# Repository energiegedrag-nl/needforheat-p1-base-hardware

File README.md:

# NeedForHeat P1-BASE hardware <!-- omit in toc -->

This repository contains the open hardware design files for the NeedForHeat P1-BASE, an extension module (BASE) for the back of an [M5Stack CoreInk](https://docs.m5stack.com/en/core/coreink). With it, the CoreInk reads [smart meters that adhere to the Dutch Smart Meter Requirements](https://github.com/energiegedrag-nl/dsmr-info) via the [P1 port](https://nl.wikipedia.org/wiki/P1-poort), while an existing P1 reader of the household keeps working.

> **Own deployment.** This repository is maintained by [energiegedrag-nl](https://github.com/energiegedrag-nl) and deployed under `energiegedrag.nl`. To run your own instance, replace `energiegedrag-nl` by your GitHub organisation and `energiegedrag.nl` by your domain (hosts used: `api.<domain>`, `manuals.<domain>`), consistently in configuration and build settings.

> **Version 3.0 (November 2026) is a design that has not been built or tested yet.** The previous version 2.7 (June 2024, with DIP switches) is available under the git tag `v2.7`. See [docs/design-v3.md](docs/design-v3.md) for the design and the list of points to verify on the first prototype.

*Top edge: smart-meter socket `J2` with its green LED, which shows through a window in the top wall of the tray. The lower socket `J3` has its own green LED in the bottom wall.*

## Table of contents <!-- omit in toc -->
- [General info](#general-info)
- [Producing](#producing)
  - [Printed Circuit Board](#printed-circuit-board)
  - [Enclosure](#enclosure)
- [Deploying](#deploying)
  - [Cost](#cost)
  - [Connecting](#connecting)
  - [Indicators](#indicators)
- [Developing](#developing)
- [Features](#features)
- [Status](#status)
- [License](#license)
- [Citation](#citation)
- [Credits](#credits)

## General info

The P1-BASE plugs into the 2x8 MI-BUS socket on the back of the CoreInk. The upper RJ12 socket (`J2`, *smart meter*) connects to the P1 port of the smart meter; the lower RJ12 socket (`J3`, *other P1 reader*) takes the cable of an existing P1 reader, as if it were connected to the meter itself.

In short (details in [docs/design-v3.md](docs/design-v3.md)):

* **Meter input** with a 1 kΩ pull-up and a Schmitt trigger, as in the v2.7 front end that read Landis+Gyr E350/E360 meters in the lab.
* **Active splitter**, powered by the meter: an existing reader keeps getting data when the CoreInk is off, asleep or crashed.
* **Data request** without DIP switches: the CoreInk (G26) and the existing reader can both request data; firmware can see whether the reader requests (G34).
* **Power from the P1 port**: on DSMR 5 meters the BASE can charge the CoreInk battery at 60 or 120 mA, switched by firmware and with a soft start that stays below the meter's fold-back limit.
* **Robust installation**: a crossed RJ12 cable or a cable in the wrong socket does no harm, and the firmware can tell which mistake was made.

The firmware is [needforheat-p1-reader-firmware](https://github.com/energiegedrag-nl/needforheat-p1-reader-firmware) (PlatformIO environment `M5STACK_COREINK_P1BASE_V3`).

## Producing

### Printed Circuit Board

The folder [pcb/jlcpcb](./pcb/jlcpcb) contains the files to have the PCB manufactured *and assembled* by [JLCPCB](https://jlcpcb.com); no soldering is needed:

1. Upload [`GERBER-needforheat-p1-base-hardware.zip`](./pcb/jlcpcb/GERBER-needforheat-p1-base-hardware.zip) on the [JLCPCB quote page](https://cart.jlcpcb.com/quote). Defaults are fine (2 layers, 1.6 mm).
2. Select *PCB Assembly*, top side, and upload [`BOM-needforheat-p1-base-hardware.csv`](./pcb/jlcpcb/BOM-needforheat-p1-base-hardware.csv) and [`CPL-needforheat-p1-base-hardware.csv`](./pcb/jlcpcb/CPL-needforheat-p1-base-hardware.csv).
3. The three through-hole parts (two RJ12 sockets, the 2x8 stacking header) are soldered by JLCPCB as well; accept the through-hole assembly option.
4. `R6` and `R15` are intentionally not fitted (see [assembly variants](docs/design-v3.md#8-production)).

Schematic and layout printouts: [docs/needforheat-p1-base-hardware-sch.pdf](docs/needforheat-p1-base-hardware-sch.pdf) and [docs/needforheat-p1-base-hardware-pcb.pdf](docs/needforheat-p1-base-hardware-pcb.pdf).

### Enclosure

The folder [enclosure](./enclosure) contains a parametric enclosure (CadQuery script) and exported STEP/STL files in [enclosure/fabrication](./enclosure/fabrication): a tray (*kuip*) that holds the PCB and a lid that clicks onto it (snap fit, no screws). The outside is exactly the CoreInk's outline (40 x 56 mm), so any BASE that fits a bare CoreInk also fits behind the P1-BASE. Four posts with crush ribs centre the module in the CoreInk's LEGO-compatible holes; the lid repeats those holes as LEGO Technic holes and has the bus socket just below its surface (0.3 mm), like the CoreInk's back; feet under the lid's corners hold the PCB down. Each socket's LED shows through a window in the wall next to it; an arrow on the lid points to the meter edge. Each module fits a letterbox parcel on its own (at most 27 mm thick). Print with PETG or let a 3D printing service make them (SLA resin or MJF nylon).

## Deploying

### Cost

Indicative, November 2026, excluding VAT and shipping. JLCPCB quotes (LeadFree HASL, top side, no panelisation;
5 pieces on 17 November after the design review, the rest on 16 November 2026; the review changed only resistor
values and J1's drill, which hardly changes the price) for the same quantities as the
[BatteryBASE](https://github.com/energiegedrag-nl/needforheat-battery-base-hardware#cost). Everything is assembled
by JLCPCB, the through-hole parts included: the quotes contain the hand-soldering fee (€ 3.27 per order) and the
per-joint manual assembly of the RJ12 jacks. The stacking header J1 (Samtec ESQ-108-24-G-D, C21241050) is not in
JLCPCB's stock: it is bought through JLCPCB's *Global Sourcing* into the account's parts library (9–15 days or more;
the prototype's seven arrive on 8 December 2026) and then assembled by JLCPCB (Samtec rates it for lead wave soldering only, so the order asks for hand
soldering with the pins kept free of solder; Economic and Standard PCBA). The J1 column adds its Global Sourcing price (€ 6.28 each, the price of the prototype's order),
its extended-part loading fee (€ 3.16 per order) and the soldering of its 16 joints (about € 0.26 per board,
JLCPCB's [per-joint rate](https://jlcpcb.com/help/article/PCB-assembly-faqs) of $ 0.0173); to be confirmed by the
quote with J1 once it is in the parts library.

| Quantity | PCBA type | PCB + PCBA without J1 | J1 (part, fee, soldering) | Per board | Enclosure (tray, lid) per set |
|---:|---|---:|---:|---:|---:|
| 5 | Economic | € 59.50 | € 35.84 | € 19.07 | $ 3.32 |
| 10 | Economic | € 79.26 | € 68.52 | € 14.78 | $ 3.32 |
| 30 | Economic | € 157.92 | € 199.24 | € 11.91 | $ 3.32 |
| 100 | Standard (Economic not offered) | € 274.37 + U5 € 185.94 | € 656.76 | € 11.17 | $ 3.32 |

J1 is the most expensive part by far. For larger series it is worth buying it cheaper: Samtec lists $ 4.10 each at
25 and $ 3.39 at 100, and JLCPCB's pre-order price is € 3.67 when a pre-order goes through (the prototype's
pre-order of 15 November 2026 was cancelled and refunded). Global Sourcing has to be ordered at least 10 pieces at a
time in the parts cart (the prototype's order of seven went through at checkout).

At 100 pieces JLCPCB had only 62 PCA9633 LED dimmers (U5) in stock: the € 274.37 is without U5, which adds about
€ 1.86 per board at JLCPCB's part price once it is in stock again. The PCA9633 is also the most expensive part at
small quantities (€ 2.78 at 5, € 2.36 at 10). Enclosure: MJF nylon prints (PA12, dyed black), which JLC3DP prices
per piece, so the price per set does not depend on the quantity (17 November 2026: tray $ 1.62, lid $ 1.70; the
prototype order adds a second lid with a firmer snap fit, $ 1.70). Shipping to the Netherlands adds about € 20–25 per
order.

| Item | Approx. price |
|---|---:|
| P1-BASE PCB, assembled (JLCPCB), J1 included | € 11–19 (see above) |
| Enclosure (3D printed, MJF nylon) | € 3 |
| M5Stack CoreInk | € 36 |
| RJ12 cable 6P6C, straight (1:1), ≤ 0.5 m | € 3–6 |
| USB power adapter (only for DSMR 2/3 meters) | € 10–15 |

### Connecting

The CoreInk and the P1-BASE are shipped separately (each fits a letterbox parcel) and clicked together at home.

1. Hold the CoreInk with its screen facing you and the HAT connector (top edge) up. Push the P1-BASE onto its back so that the *smart meter* socket is at the top (the arrow on the lid points up); it only fits this way round.
2. Unplug an existing P1 reader (if any) from the smart meter.
3. Plug the supplied **straight (1:1)** RJ12 cable into the *smart meter* socket and into the P1 port of the smart meter. Do not use a telephone cable: those are crossed. A crossed cable does no damage, but nothing works; the screen will say so.
4. Plug the existing P1 reader into the lower *other P1 reader* socket.

With a DSMR 2 or 3 meter (no power on the P1 port), also connect the USB power adapter to the CoreInk.

### Indicators

Each socket has a green light next to it: **it blinks when data goes over that cable.**

| Green light next to | Blinks | Stays dark (or lights steadily): check |
|---|---|---|
| *smart meter* socket (top) | the meter sends data | the cable to the meter; whether the meter's P1 port is enabled (with no cable, or a meter that is not asked for data, it can light steadily) |
| *other P1 reader* socket (bottom) | the existing P1 reader asks for data and gets it | whether a reader is plugged in and powered; its cable |

Charging the CoreInk battery from the P1 port (DSMR 5 meters) is shown on the screen.

Firmware can dim both LEDs together or switch them off (I²C LED driver, see [LED dimmer](docs/design-v3.md#47-led-dimmer)); the hardware still decides when each LED is on. The driver is powered by the meter, so the setting survives while the CoreInk sleeps or is off; until firmware sets it (and after the meter's power was lost), the LEDs light at full brightness.

## Developing

You need [KiCad 10](https://www.kicad.org/download/) to change the design; the KiCad files are in [pcb](./pcb).

The schematic and the board are generated by scripts in [tools](./tools), so that the netlist, the placement and the documentation stay consistent:

* `python tools/gen_schematic.py` writes the schematic and the custom symbol library from the circuit description in the script.
* `"<KiCad>/bin/python.exe" tools/gen_pcb.py` builds the board from the schematic netlist, places the parts and routes the board with [Freerouting](https://github.com/freerouting/freerouting) (Java 25 needed).
* `python tools/sim/run_sims.py` runs SPICE checks with the ngspice library that ships with KiCad and writes [docs/simulation](docs/simulation).
* `python tools/export_fab.py` writes the JLCPCB files and the PDF printouts.
* 3D models in `pcb/p1base.3dshapes`: J1 is Samtec's own model of the ESQ-108-24-G-D (downloaded from the
  [product page](https://www.samtec.com/products/esq-108-24-g-d), provided "as is"; placed by
  `python tools/import_samtec_j1.py <esq-108-24-g-d.stp>`). EVERCOM publishes no 3D model of the RJ12 jack
  5301-6P6C, so `python tools/gen_3d_models.py` builds an approximate one from its drawing (5301-660XXX rev. A).

You may also edit the KiCad files by hand; then stop using the generators or port your changes into them.

## Features

Ready (in the design, not yet verified on hardware):

- [x] Active P1 splitter powered by the meter, open-drain output as DSMR prescribes.
- [x] Data request by firmware and by the existing reader (hardware OR); read-back of the reader's request.
- [x] Charging the CoreInk battery from DSMR 5 meters at 60/120 mA with soft start.
- [x] Protection against crossed cables and ESD; meter voltage measurement for diagnosis.
- [x] A green LED next to each socket that blinks when data goes over that cable; dimmable by firmware (one common level); test points.
- [x] All parts on the top side; full assembly by JLCPCB.
- [x] Enclosure flush with the CoreInk outline, so other CoreInk BASEs still stack behind it; snap-fit lid with LEGO Technic holes.

To-do:

- [ ] Build and test a first prototype (see [the list of points to verify](docs/design-v3.md#10-open-points-to-verify)), including Landis+Gyr E360 meters and common P1 readers on the second socket.

## Status

Project is: _in progress_ (v3.0 design; v2.7 built and lab-tested in 2024).

## License

The hardware designs in this repository are available under the [CERN-OHL-P v2 license](./LICENSE).
Copyright 2024 [Research group Energy Transition, Windesheim University of Applied Sciences](https://windesheim.nl/energietransitie) (up to v2.7); copyright 2026 Henri ter Hofte (v3.0).

## Citation

If you use this repository in your research or work, please cite the following pre-print, which describes the overall NeedForHeat DataGear system of which this repository is a part:

> Ter Hofte, H., & van Ravenzwaaij, N. (2025). *NeedForHeat DataGear: An Open Monitoring System to Accelerate the Residential Heating Transition*. arXiv preprint arXiv:2509.06927. https://doi.org/10.48550/arXiv.2509.06927

**Note:** This is a pre-print submitted on 8 Sep 2025 and has not yet been peer-reviewed. For the full paper, see [https://arxiv.org/abs/2509.06927](https://arxiv.org/abs/2509.06927).

## Credits

Version 3.0:
* Henri ter Hofte · [@henriterhofte](https://github.com/henriterhofte)

Version 2.7 and earlier, made at the Research group Energy Transition, Windesheim University of Applied Sciences, as a collaborative effort of:
* Rick de Graaf · [@277r](https://github.com/277r)
* Gerwin ten Have · [@GerwintenHave](https://github.com/GerwintenHave)

with product owners:
* Henri ter Hofte · [@henriterhofte](https://github.com/henriterhofte)
* Marco Winkelman · [@MarcoW71](https://github.com/MarcoW71)

We use and gratefully acknowledge the efforts of the makers of:
* [Twomes P1 Gateway Hardware](https://github.com/energiegedrag-nl/twomes-p1-gateway-hardware), by Research group Energy Transition at Windesheim University of Applied Sciences, licensed under Apache 2.0
* [KiCad Libraries](https://kicad.github.io/), by the KiCad Development Team, licensed under [an adapted version of the CC-BY-SA 4.0 License](https://www.kicad.org/libraries/license/)
* [Freerouting](https://github.com/freerouting/freerouting), licensed under GPL-3.0 (used as a tool; no code included)
* [ngspice](https://ngspice.sourceforge.io/) and [CadQuery](https://github.com/CadQuery/cadquery) (used as tools)
* The mechanical data of the [M5Stack CoreInk](https://github.com/m5stack/M5_Hardware), by M5Stack

### AI assistance

Since November 2026, parts of this repository (the v3.0 design, its generators and documentation) have been made with [Claude Code](https://claude.com/claude-code) (Anthropic), under the author's direction and review. Commits made this way carry a `Co-Authored-By: Claude …` trailer. The author remains responsible for all content.

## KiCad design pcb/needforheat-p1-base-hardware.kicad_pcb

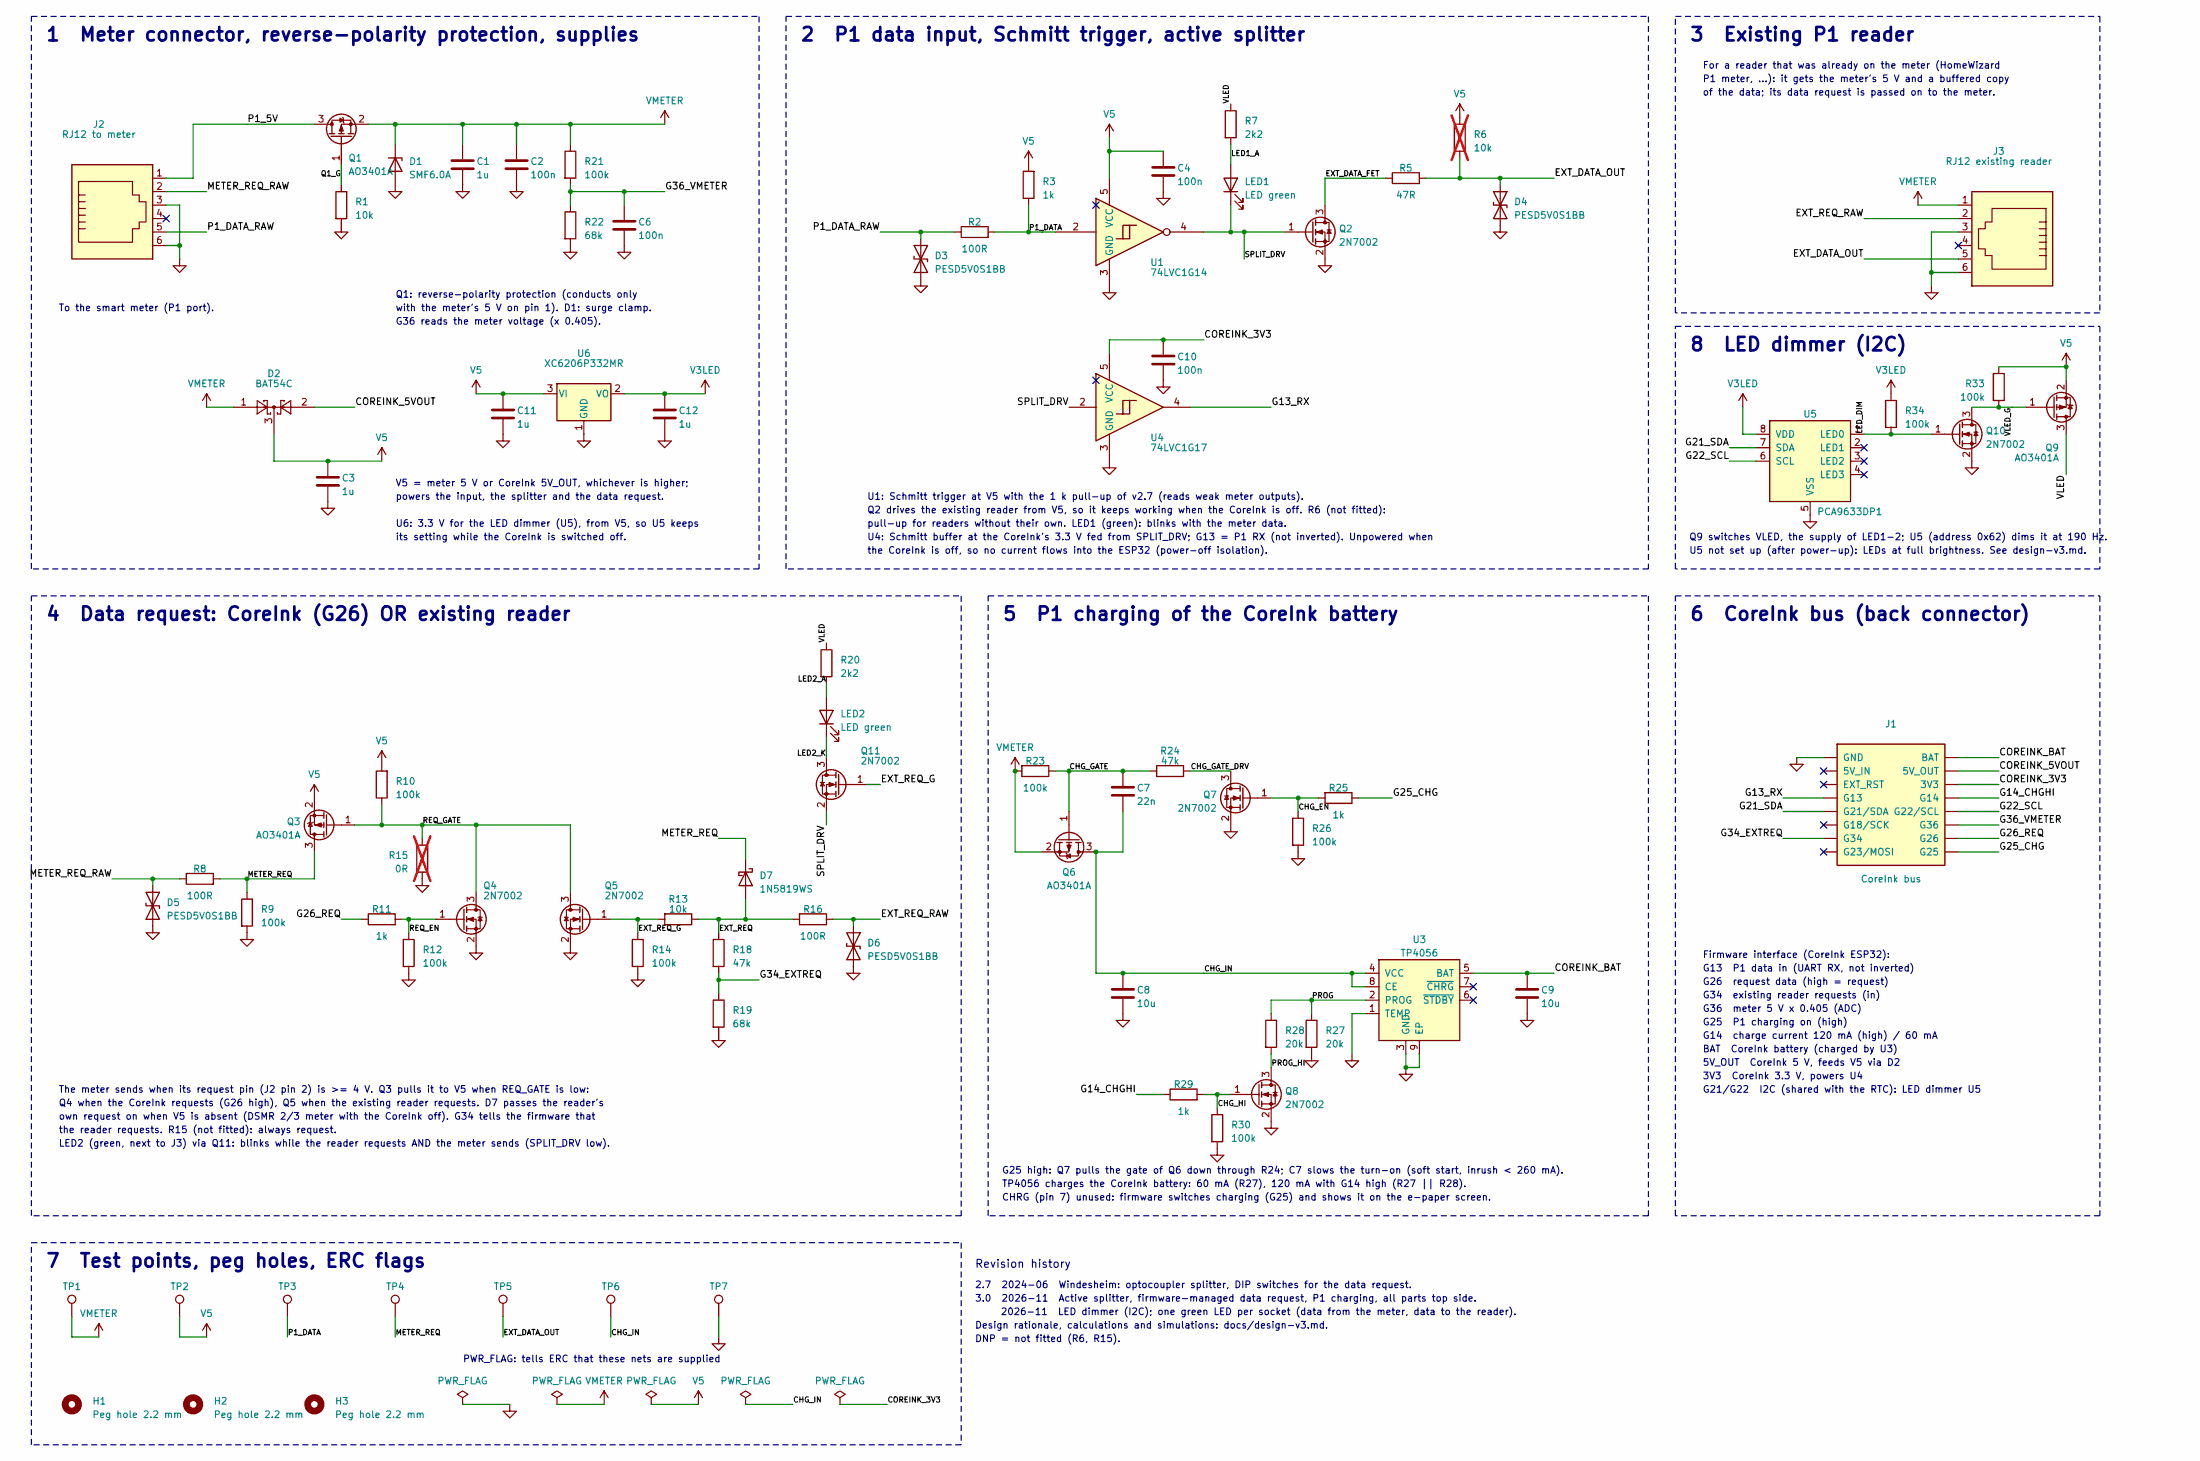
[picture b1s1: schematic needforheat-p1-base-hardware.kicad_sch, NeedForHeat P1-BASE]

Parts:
C1, C3, C11, C12: 1u; C_0603_1608Metric; LCSC C15849
C2, C4, C6, C10: 100n; C_0603_1608Metric; LCSC C14663
C7: 22n; C_0603_1608Metric; LCSC C21122
C8, C9: 10u; C_0805_2012Metric; LCSC C15850
D1: SMF6.0A; D_SMF; LCSC C178260
D2: BAT54C; SOT-23; LCSC C37704
D3, D4, D5, D6: PESD5V0S1BB; D_SOD-523; LCSC C2687128
D7: 1N5819WS; D_SOD-323; LCSC C191023
H1, H2, H3: Peg hole 2.2 mm; PegHole_2.2mm_NPTH
J1: CoreInk bus; CoreInk_Bus_2x08_P2.54mm; LCSC C21241050
J2: RJ12 to meter; RJ12_EVERCOM_5301-6P6C; LCSC C3097716
J3: RJ12 existing reader; RJ12_EVERCOM_5301-6P6C; LCSC C3097716
LED1, LED2: LED green; LED_LiteOn_LTST-S220_SideView; LCSC C160469
Q1, Q3, Q6, Q9: AO3401A; SOT-23; LCSC C15127
Q2, Q4, Q5, Q7, Q8, Q10, Q11: 2N7002; SOT-23; LCSC C8545
R1, R13: 10k; R_0603_1608Metric; LCSC C25804
R2, R8, R16: 100R; R_0603_1608Metric; LCSC C22775
R3, R11, R25, R29: 1k; R_0603_1608Metric; LCSC C21190
R5: 47R; R_0603_1608Metric; LCSC C23182
R6: 10k; R_0603_1608Metric; LCSC C25804; not fitted
R7, R20: 2k2; R_0603_1608Metric; LCSC C4190
R9, R10, R12, R14, R21, R23, R26, R30, R33, R34: 100k; R_0603_1608Metric; LCSC C25803
R15: 0R; R_0603_1608Metric; LCSC C21189; not fitted
R18, R24: 47k; R_0603_1608Metric; LCSC C25819
R19, R22: 68k; R_0603_1608Metric; LCSC C23231
R27, R28: 20k; R_0603_1608Metric; LCSC C4184
TP1: VMETER; TestPoint_Pad_D1.0mm
TP2: V5; TestPoint_Pad_D1.0mm
TP3: P1_DATA; TestPoint_Pad_D1.0mm
TP4: METER_REQ; TestPoint_Pad_D1.0mm
TP5: EXT_DATA_OUT; TestPoint_Pad_D1.0mm
TP6: CHG_IN; TestPoint_Pad_D1.0mm
TP7: GND; TestPoint_Pad_D1.0mm
U1: 74LVC1G14; SOT-23-5; LCSC C7835
U3: TP4056; SOIC-8-1EP_3.9x4.9mm_P1.27mm_EP2.29x3mm; LCSC C16581
U4: 74LVC1G17; SOT-23-5; LCSC C7836
U5: PCA9633DP1; TSSOP-8_3x3mm_P0.65mm; LCSC C88381
U6: XC6206P332MR; SOT-23-3; LCSC C5446

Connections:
/CHG_EN: Q7.1 (G), R25.2, R26.1
/CHG_GATE: C7.1, Q6.1 (G), R23.1, R24.1
/CHG_GATE_DRV: Q7.3 (D), R24.2
/CHG_HI: Q8.1 (G), R29.2, R30.1
/CHG_IN: C7.2, C8.1, Q6.3 (D), TP6.1, U3.4 (VCC), U3.8 (CE)
/COREINK_3V3: C10.1, J1.3V3, U4.5 (VCC)
/COREINK_5VOUT: D2.2, J1.5VOUT (5V_OUT)
/COREINK_BAT: C9.1, J1.BAT, U3.5 (BAT)
/EXT_DATA_FET: Q2.3 (D), R5.1
/EXT_DATA_OUT: D4.1 (A1), J3.5, R5.2, R6.1, TP5.1
/EXT_REQ: D7.2 (A), R13.1, R16.2, R18.1
/EXT_REQ_G: Q5.1 (G), Q11.1 (G), R13.2, R14.1
/EXT_REQ_RAW: D6.1 (A1), J3.2, R16.1
/G13_RX: J1.G13, U4.4
/G14_CHGHI: J1.G14, R29.1
/G21_SDA: J1.G21 (G21/SDA), U5.7 (SDA)
/G22_SCL: J1.G22 (G22/SCL), U5.6 (SCL)
/G25_CHG: J1.G25, R25.1
/G26_REQ: J1.G26, R11.1
/G34_EXTREQ: J1.G34, R18.2, R19.1
/G36_VMETER: C6.1, J1.G36, R21.2, R22.1
/LED1_A: LED1.2 (A), R7.2
/LED2_A: LED2.2 (A), R20.2
/LED2_K: LED2.1 (K), Q11.3 (D)
/LED_DIM: Q10.1 (G), R34.2, U5.1 (LED0)
/METER_REQ: D7.1 (K), Q3.3 (D), R8.2, R9.1, TP4.1
/METER_REQ_RAW: D5.1 (A1), J2.2, R8.1
/P1_5V: J2.1, Q1.3 (D)
/P1_DATA: R2.2, R3.1, TP3.1, U1.2
/P1_DATA_RAW: D3.1 (A1), J2.5, R2.1
/PROG: R27.1, R28.1, U3.2 (PROG)
/PROG_HI: Q8.3 (D), R28.2
/Q1_G: Q1.1 (G), R1.1
/REQ_EN: Q4.1 (G), R11.2, R12.1
/REQ_GATE: Q3.1 (G), Q4.3 (D), Q5.3 (D), R10.1, R15.1
/SPLIT_DRV: LED1.1 (K), Q2.1 (G), Q11.2 (S), U1.4, U4.2
/VLED: Q9.3 (D), R7.1, R20.1
/VLED_G: Q9.1 (G), Q10.3 (D), R33.2
GND: C1.2, C2.2, C3.2, C4.2, C6.2, C8.2, C9.2, C10.2, C11.2, C12.2, D1.2 (A), D3.2 (A2), D4.2 (A2), D5.2 (A2), D6.2 (A2), J1.GND, J2.3, J2.6, J3.3, J3.6, Q2.2 (S), Q4.2 (S), Q5.2 (S), Q7.2 (S), Q8.2 (S), Q10.2 (S), R1.2, R9.2, R12.2, R14.2, R15.2, R19.2, R22.2, R26.2, R27.2, R30.2, TP7.1, U1.3 (GND), U3.1 (TEMP), U3.3 (GND), U3.9 (EP), U4.3 (GND), U5.5 (VSS), U6.1 (GND)
V3LED: C12.1, R34.1, U5.8 (VDD), U6.2 (VO)
V5: C3.1, C4.1, C11.1, D2.3, Q3.2 (S), Q9.2 (S), R3.2, R6.2, R10.2, R33.1, TP2.1, U1.5 (VCC), U6.3 (VI)
VMETER: C1.1, C2.1, D1.1 (K), D2.1, J3.1, Q1.2 (S), Q6.2 (S), R21.1, R23.2, TP1.1

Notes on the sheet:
1 Meter connector, reverse-polarity protection, supplies
To the smart meter (P1 port).
Q1: reverse-polarity protection (conducts only
with the meter's 5 V on pin 1). D1: surge clamp.
G36 reads the meter voltage (x 0.405).
V5 = meter 5 V or CoreInk 5V_OUT, whichever is higher;
powers the input, the splitter and the data request.
U6: 3.3 V for the LED dimmer (U5), from V5, so U5 keeps
its setting while the CoreInk is switched off.
2 P1 data input, Schmitt trigger, active splitter
U1: Schmitt trigger at V5 with the 1 k pull-up of v2.7 (reads weak meter outputs).
Q2 drives the existing reader from V5, so it keeps working when the CoreInk is off. R6 (not fitted):
pull-up for readers without their own. LED1 (green): blinks with the meter data.
U4: Schmitt buffer at the CoreInk's 3.3 V fed from SPLIT_DRV; G13 = P1 RX (not inverted). Unpowered when
the CoreInk is off, so no current flows into the ESP32 (power-off isolation).
3 Existing P1 reader
For a reader that was already on the meter (HomeWizard
P1 meter, ...): it gets the meter's 5 V and a buffered copy
of the data; its data request is passed on to the meter.
8 LED dimmer (I2C)
Q9 switches VLED, the supply of LED1-2; U5 (address 0x62) dims it at 190 Hz.
U5 not set up (after power-up): LEDs at full brightness. See design-v3.md.
4 Data request: CoreInk (G26) OR existing reader
The meter sends when its request pin (J2 pin 2) is >= 4 V. Q3 pulls it to V5 when REQ_GATE is low:
Q4 when the CoreInk requests (G26 high), Q5 when the existing reader requests. D7 passes the reader's
own request on when V5 is absent (DSMR 2/3 meter with the CoreInk off). G34 tells the firmware that
the reader requests. R15 (not fitted): always request.
LED2 (green, next to J3) via Q11: blinks while the reader requests AND the meter sends (SPLIT_DRV low).
5 P1 charging of the CoreInk battery
G25 high: Q7 pulls the gate of Q6 down through R24; C7 slows the turn-on (soft start, inrush < 260 mA).
TP4056 charges the CoreInk battery: 60 mA (R27), 120 mA with G14 high (R27 || R28).
CHRG (pin 7) unused: firmware switches charging (G25) and shows it on the e-paper screen.
6 CoreInk bus (back connector)
Firmware interface (CoreInk ESP32):
G13 P1 data in (UART RX, not inverted)
G26 request data (high = request)
G34 existing reader requests (in)
G36 meter 5 V x 0.405 (ADC)
G25 P1 charging on (high)
G14 charge current 120 mA (high) / 60 mA

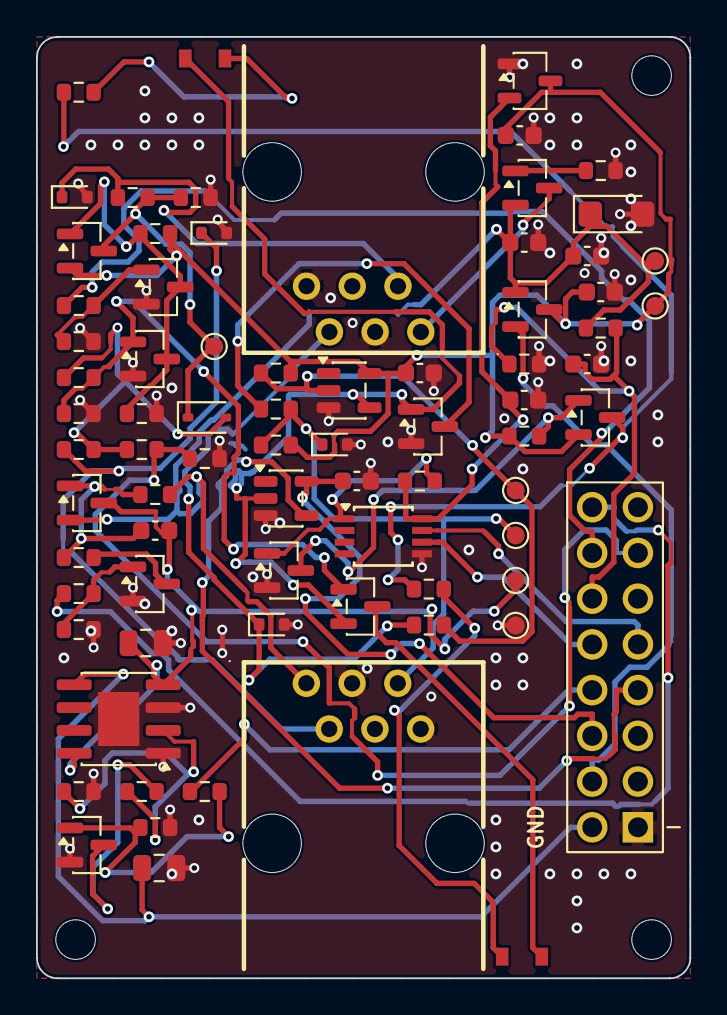
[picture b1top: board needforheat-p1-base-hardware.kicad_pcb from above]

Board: 2 copper layers, 36.3 x 52.3 mm, 79 parts (0 on the bottom side), 42 nets.

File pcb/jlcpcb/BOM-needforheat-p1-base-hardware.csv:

Comment,Designator,Footprint,LCSC
1u,"C1,C3,C11,C12",C_0603_1608Metric,C15849
100n,"C2,C4,C6,C10",C_0603_1608Metric,C14663
22n,C7,C_0603_1608Metric,C21122
10u,"C8,C9",C_0805_2012Metric,C15850
SMF6.0A,D1,D_SMF,C178260
BAT54C,D2,SOT-23,C37704
PESD5V0S1BB,"D3,D4,D5,D6",D_SOD-523,C2687128
1N5819WS,D7,D_SOD-323,C191023
CoreInk bus,J1,CoreInk_Bus_2x08_P2.54mm,C21241050
RJ12 to meter / RJ12 existing reader,"J2,J3",RJ12_EVERCOM_5301-6P6C,C3097716
LED green,"LED1,LED2",LED_LiteOn_LTST-S220_SideView,C160469
AO3401A,"Q1,Q3,Q6,Q9",SOT-23,C15127
2N7002,"Q2,Q4,Q5,Q7,Q8,Q10,Q11",SOT-23,C8545
10k,"R1,R13",R_0603_1608Metric,C25804
100R,"R2,R8,R16",R_0603_1608Metric,C22775
1k,"R3,R11,R25,R29",R_0603_1608Metric,C21190
47R,R5,R_0603_1608Metric,C23182
2k2,"R7,R20",R_0603_1608Metric,C4190
100k,"R9,R10,R12,R14,R21,R23,R26,R30,R33,R34",R_0603_1608Metric,C25803
47k,"R18,R24",R_0603_1608Metric,C25819
68k,"R19,R22",R_0603_1608Metric,C23231
20k,"R27,R28",R_0603_1608Metric,C4184
74LVC1G14,U1,SOT-23-5,C7835
TP4056,U3,SOIC-8-1EP_3.9x4.9mm_P1.27mm_EP2.29x3mm,C16581
74LVC1G17,U4,SOT-23-5,C7836
PCA9633DP1,U5,TSSOP-8_3x3mm_P0.65mm,C88381
XC6206P332MR,U6,SOT-23-3,C5446

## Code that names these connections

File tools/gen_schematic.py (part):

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    s.place("R22", 116.84, 54.61)
    s.place("C6", 127.0, 54.61)
    s.wire("J2.1", (45.72, 45.72), (45.72, 35.56), (55.88, 35.56), "Q1.3", first="v")
    s.label("P1_5V", (55.88, 35.56))
    s.wire("Q1.1", (73.66, 45.72), "R1.1")
    s.label("Q1_G", (73.66, 45.72), "l", 1.0)
    s.power("GND", "R1.2")
    s.wire("Q1.2", (83.82, 35.56), (96.52, 35.56), (106.68, 35.56), (116.84, 35.56), (134.62, 35.56))
    s.power("VMETER", (134.62, 35.56))
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    s.wire("R21.2", (116.84, 48.26), "R22.1")
    s.wire((116.84, 48.26), (127.0, 48.26), (134.62, 48.26))
    s.wire((127.0, 48.26), "C6.1")
    s.label("G36_VMETER", (134.62, 48.26))
    s.wire("J2.3", (43.18, 50.8), (43.18, 58.42), (43.18, 60.96))
    s.wire("J2.6", (43.18, 58.42))
    s.power("GND", (43.18, 60.96))
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    s.place("U4", 210.82, 88.9)
    s.place("C10", 215.9, 80.01)
    s.wire((162.56, 55.88), (170.18, 55.88), "R2.1")
    s.label("P1_DATA_RAW", (162.56, 55.88), "l")
    s.wire((170.18, 55.88), "D3.1")
    s.power("GND", "D3.2")
    s.wire("R2.2", (190.5, 55.88), (193.04, 55.88), "U1.2")
    s.label("P1_DATA", (190.5, 55.88), "r", 1.0)
    s.wire("R3.1", (190.5, 55.88))
    s.power("V5", "R3.2")
    s.wire("U1.5", (205.74, 40.64), (205.74, 38.1))
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    s.power("GND", "U1.3")
    s.wire("U1.4", (228.6, 55.88), (231.14, 55.88), "Q2.1")
    s.wire((231.14, 55.88), (231.14, 60.96))
    s.label("SPLIT_DRV", (231.14, 60.96), "r", 1.0)
    s.wire("LED1.1", (228.6, 55.88))
    s.wire("LED1.2", (228.6, 41.91), "R7.2")
    s.label("LED1_A", (228.6, 41.91), "r", 1.0)
    s.label("VLED", "R7.1", "u", 1.0)
    s.power("GND", "Q2.2")
    s.wire("Q2.3", (246.38, 45.72), "R5.1", first="v")
    s.label("EXT_DATA_FET", (246.38, 45.72), "r", 1.0)
    s.wire("R5.2", (271.78, 45.72), (279.4, 45.72), (289.56, 45.72))
    s.wire("R6.1", (271.78, 45.72))
    s.power("V5", "R6.2")
    s.wire((279.4, 45.72), "D4.1")
    s.power("GND", "D4.2")
    s.label("EXT_DATA_OUT", (289.56, 45.72))
    s.wire("U4.5", (205.74, 76.2), (215.9, 76.2), (223.52, 76.2))
    s.wire((215.9, 76.2), "C10.1")
    s.power("GND", "C10.2")
    s.label("COREINK_3V3", (223.52, 76.2))
    s.power("GND", "U4.3")
    s.label("SPLIT_DRV", "U4.2", "l")
    s.wire("U4.4", (236.22, 88.9))
    s.label("G13_RX", (236.22, 88.9))
    s.note("U1: Schmitt trigger at V5 with the 1 k pull-up of v2.7 (reads weak meter outputs).", 160.02, 106.68)
    s.note("Q2 drives the existing reader from V5, so it keeps working when the CoreInk is off. R6 (not fitted):", 160.02, 109.22)
    s.note("pull-up for readers without their own. LED1 (green): blinks with the meter data.", 160.02, 111.76)
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    s.power("GND", "U5.5")
    s.wire("U5.1", (365.76, 93.98), "Q10.1")
    s.wire("R34.2", (365.76, 93.98))
    s.label("LED_DIM", "U5.1", "u", 1.0)
    s.power("V3LED", "R34.1")
    s.power("GND", "Q10.2")
    s.wire("Q10.3", (386.08, 88.9), (388.62, 88.9))
    s.wire((388.62, 88.9), "Q9.1")
    s.wire("R33.2", (386.08, 88.9))
    s.label("VLED_G", (388.62, 88.9), "d", 1.0)
    s.wire("R33.1", (398.78, 81.28), "Q9.2")
    s.power("V5", (398.78, 81.28))
    s.wire("Q9.3", (398.78, 101.6))
    s.label("VLED", (398.78, 101.6), "d")
    s.note("Q9 switches VLED, the supply of LED1-2; U5 (address 0x62) dims it at 190 Hz.", 327.66, 114.3)
    s.note("U5 not set up (after power-up): LEDs at full brightness. See design-v3.md.", 327.66, 116.84)

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    s.place("R16", 154.94, 185.42, rot=270)
    s.place("D6", 162.56, 190.5, rot=270)
    s.wire((22.86, 177.8), (30.48, 177.8), "R8.1")
    s.label("METER_REQ_RAW", (22.86, 177.8), "l")
    s.wire((30.48, 177.8), "D5.1")
    s.power("GND", "D5.2")
    s.wire("R8.2", (48.26, 177.8), (60.96, 177.8), "Q3.3")
    s.label("METER_REQ", (48.26, 177.8), "r", 1.0)
    s.wire((48.26, 177.8), "R9.1")
    s.power("GND", "R9.2")
    s.power("V5", "Q3.2")
    s.wire("Q3.1", (73.66, 167.64), (81.28, 167.64), (91.44, 167.64), (109.22, 167.64))
    s.label("REQ_GATE", (81.28, 167.64), "r", 1.0)
    s.wire("R10.1", (73.66, 167.64))
    s.power("V5", "R10.2")
    s.wire((81.28, 167.64), "R15.1")
    s.power("GND", "R15.2")
    s.wire("LED2.1", "Q11.3")
    s.label("LED2_K", "Q11.3", "l", 1.0)
    s.stub("Q11.1", "EXT_REQ_G", 2.54, "r")
    s.stub("Q11.2", "SPLIT_DRV", 2.54, "d")
    s.wire("LED2.2", "R20.2")
    s.label("LED2_A", "R20.2", "l", 1.0)
    s.label("VLED", "R20.1", "u", 1.0)
    s.wire("Q4.3", (91.44, 167.64))
    s.power("GND", "Q4.2")
    s.wire((66.04, 185.42), "R11.1")
    s.label("G26_REQ", (66.04, 185.42), "l")
    s.wire("R11.2", (78.74, 185.42), "Q4.1")
    s.wire((78.74, 185.42), "R12.1")
    s.label("REQ_EN", "R12.1", "r", 1.0)
    s.power("GND", "R12.2")
    s.wire("Q5.3", (109.22, 167.64))
    s.power("GND", "Q5.2")
    s.wire("Q5.1", (121.92, 185.42), "R13.2")
    s.wire((121.92, 185.42), "R14.1")
    s.label("EXT_REQ_G", "R14.1", "r", 1.0)
    s.power("GND", "R14.2")
    s.wire("R13.1", (137.16, 185.42), (142.24, 185.42), "R16.2")
    s.wire((137.16, 185.42), "R18.1")
    s.label("EXT_REQ", "R18.1", "r", 1.0)
    s.wire((142.24, 185.42), "D7.2")
    s.wire("D7.1", (142.24, 170.18), (137.16, 170.18))
    s.label("METER_REQ", (137.16, 170.18), "l")
    s.wire("R18.2", (137.16, 196.85), "R19.1")
    s.wire((137.16, 196.85), (144.78, 196.85))
    s.label("G34_EXTREQ", (144.78, 196.85))
    s.power("GND", "R19.2")
    s.wire("R16.1", (162.56, 185.42), (167.64, 185.42))
    s.wire((162.56, 185.42), "D6.1")
    s.power("GND", "D6.2")
    s.label("EXT_REQ_RAW", (167.64, 185.42))
    s.note("The meter sends when its request pin (J2 pin 2) is >= 4 V. Q3 pulls it to V5 when REQ_GATE is low:", 12.7, 218.44)
    s.note("Q4 when the CoreInk requests (G26 high), Q5 when the existing reader requests. D7 passes the reader's", 12.7, 220.98)
    s.note("own request on when V5 is absent (DSMR 2/3 meter with the CoreInk off). G34 tells the firmware that", 12.7, 223.52)
    s.note("the reader requests. R15 (not fitted): always request.", 12.7, 226.06)
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    s.wire("R23.2", (200.66, 172.72), "Q6.2", first="v")
    s.power("VMETER", "R23.2")
    s.wire("R23.1", (210.82, 157.48), (220.98, 157.48), "R24.1")
    s.label("CHG_GATE", (210.82, 157.48), "r", 1.0)
    s.wire("Q6.1", (210.82, 157.48))
    s.wire("C7.1", (220.98, 157.48))
    s.wire("R24.2", "Q7.3")
    s.label("CHG_GATE_DRV", "R24.2", "r", 1.0)
    s.power("GND", "Q7.2")
    s.wire("Q7.1", (254.0, 162.56), "R25.2")
    s.wire((254.0, 162.56), "R26.1")
    s.label("CHG_EN", "R26.1", "r", 1.0)
    s.power("GND", "R26.2")
    s.wire("R25.1", (271.78, 162.56))
    s.label("G25_CHG", (271.78, 162.56))
    s.wire("C7.2", (220.98, 172.72), "Q6.3")
    s.wire("Q6.3", (215.9, 195.58), (220.98, 195.58), (236.22, 195.58), (264.16, 195.58), "U3.4", first="v")
    s.label("CHG_IN", (236.22, 195.58), "r", 1.0)
    s.wire((220.98, 195.58), "C8.1")
    s.power("GND", "C8.2")
    s.wire("U3.8", (264.16, 198.12), (264.16, 195.58))
    s.wire("U3.1", (264.16, 203.2), (264.16, 210.82))
    s.power("GND", (264.16, 210.82))
    s.wire("U3.2", (256.54, 200.66), (248.92, 200.66))
    s.label("PROG", (256.54, 200.66), "r", 1.0)
    s.wire((256.54, 200.66), "R27.1")
    s.power("GND", "R27.2")
    s.wire((248.92, 200.66), "R28.1")
    s.wire("R28.2", "Q8.3")
    s.label("PROG_HI", "Q8.3", "r", 1.0)
    s.power("GND", "Q8.2")
    s.wire("R29.2", (238.76, 218.44), "Q8.1")
    s.wire((238.76, 218.44), "R30.1")
    s.label("CHG_HI", "R30.1", "r", 1.0)
    s.power("GND", "R30.2")
    s.wire((223.52, 218.44), "R29.1")
    s.label("G14_CHGHI", (223.52, 218.44), "l")
    x3, y3 = s.pin("U3.3")
    s.wire("U3.3", (x3, y3 + 2.54), "U3.9", first="h")
    s.power("GND", (x3, y3 + 2.54))
    s.wire("U3.5", (297.18, 195.58), (302.26, 195.58))
    s.wire((297.18, 195.58), "C9.1")
    s.power("GND", "C9.2")
    s.label("COREINK_BAT", (302.26, 195.58))
    s.note("G25 high: Q7 pulls the gate of Q6 down through R24; C7 slows the turn-on (soft start, inrush < 260 mA).", 198.12, 233.68)
    s.note("TP4056 charges the CoreInk battery: 60 mA (R27), 120 mA with G14 high (R27 || R28).", 198.12, 236.22)
    s.note("CHRG (pin 7) unused: firmware switches charging (G25) and shows it on the e-paper screen.", 198.12, 238.76)
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    s.stub("J1.G34", "G34_EXTREQ", 7.62, "l")
    s.stub("J1.G21", "G21_SDA", 7.62, "l")
    s.stub("J1.G22", "G22_SCL", 7.62)
    for pin, net in (("BAT", "COREINK_BAT"), ("5VOUT", "COREINK_5VOUT"), ("3V3", "COREINK_3V3"), ("G14", "G14_CHGHI"), ("G36", "G36_VMETER"),
                     ("G26", "G26_REQ"), ("G25", "G25_CHG")):
        s.stub("J1." + pin, net, 7.62)
    for i, t in enumerate(["Firmware interface (CoreInk ESP32):",
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

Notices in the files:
pcb/needforheat-p1-base-hardware.kicad_pcb:
energiegedrag.nl - CERN-OHL-P v2
pcb/needforheat-p1-base-hardware.kicad_sch:
Licensed under CERN-OHL-P v2
